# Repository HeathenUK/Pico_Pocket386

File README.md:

All credit to Ian Scott (https://github.com/polpo/picogus) and in turn to those he credits.

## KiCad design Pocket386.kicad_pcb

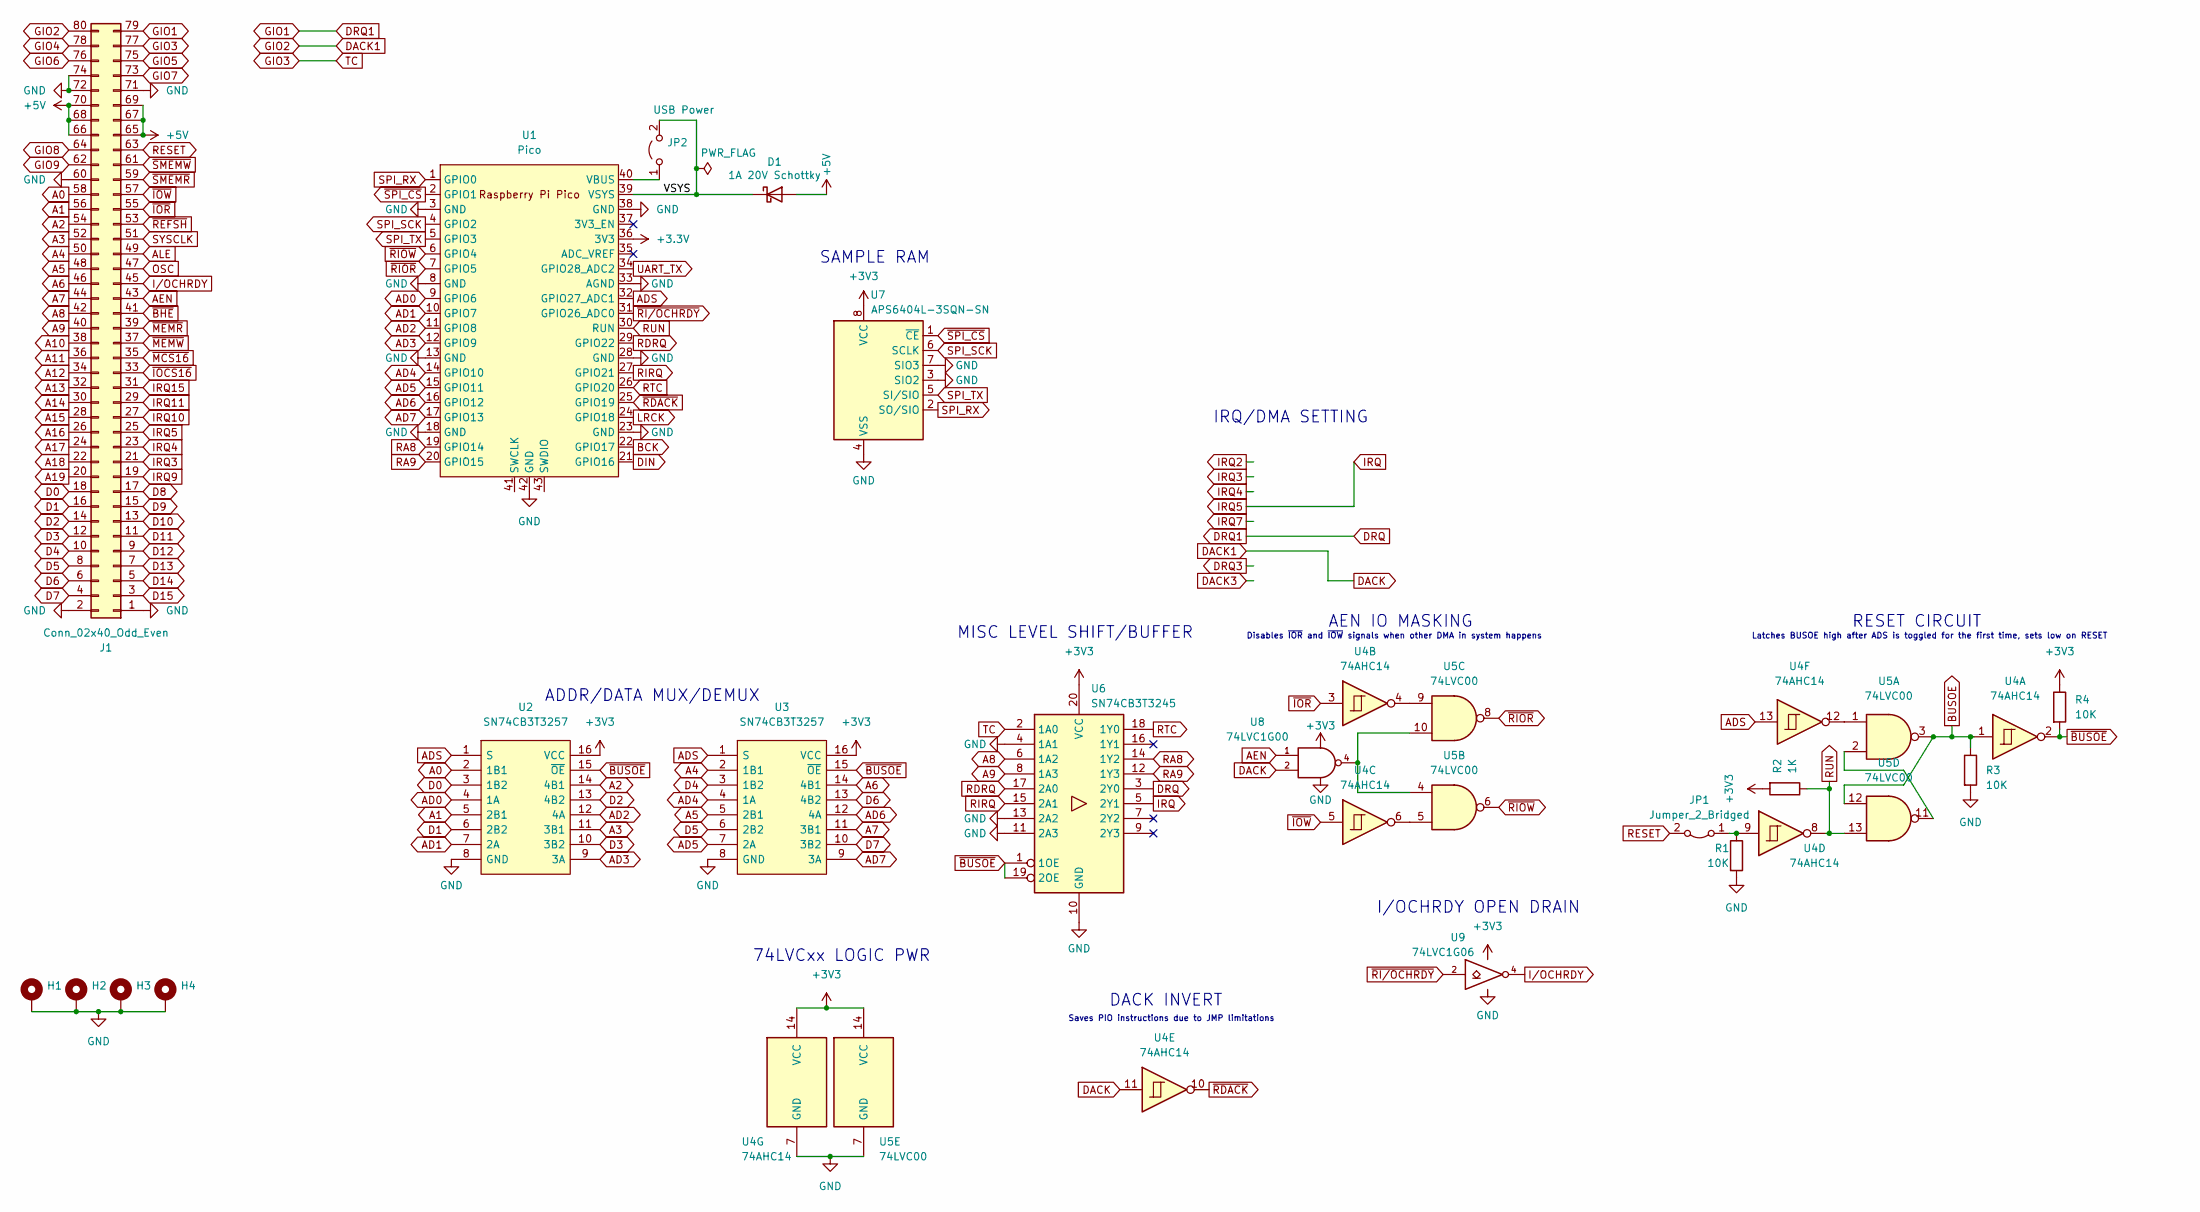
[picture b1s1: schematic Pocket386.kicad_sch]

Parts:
D1: 1A 20V Schottky; D_SOD-123
H1, H2, H3, H4: MountingHole_2.2mm_M2_Pad
J1: Conn_02x40_Odd_Even; XKB Male 80P 0.5P
JP1: Jumper_2_Bridged; PinHeader_1x02_P2.54mm_Vertical
JP2: USB Power; PinHeader_1x02_P2.54mm_Vertical
R1, R3, R4: 10K; R_0402_1005Metric
R2: 1K; R_0402_1005Metric
U1: Pico; RPi_Pico_SMD_TH
U2, U3: SN74CB3T3257; TSSOP-16_4.4x5mm_P0.65mm; Manufacturer_Part_Number 74FST3257DR2G; Mouser Part Number 863-74FST3257DR2G
U4: 74AHC14; TSSOP-14_4.4x5mm_P0.65mm
U5: 74LVC00; TSSOP-14_4.4x5mm_P0.65mm
U6: SN74CB3T3245; TSSOP-20_4.4x6.5mm_P0.65mm
U7: APS6404L-3SQN-SN; SOIC-8_3.9x4.9mm_P1.27mm
U8: 74LVC1G00; SOT-23-5
U9: 74LVC1G06; SOT-23-5

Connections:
+3.3V: U1.36 (3V3)
+3V3: R2.2, R4.1, U2.16 (VCC), U3.16 (VCC), U4.14 (VCC), U5.14 (VCC), U6.20 (VCC), U7.8 (VCC), U8.5 (VCC), U9.5 (VCC)
+5V: D1.2 (A), J1.65, J1.66, J1.67, J1.68, J1.69, J1.70
/VSYS: D1.1 (K), JP2.2 (B), U1.39 (VSYS)
A0: J1.58, U2.2 (1B1)
A1: J1.56, U2.5 (2B1)
A2: J1.54, U2.14 (4B1)
A3: J1.52, U2.11 (3B1)
A4: J1.50, U3.2 (1B1)
A5: J1.48, U3.5 (2B1)
A6: J1.46, U3.14 (4B1)
A7: J1.44, U3.11 (3B1)
A8: J1.42, U6.6 (1A2)
A9: J1.40, U6.8 (1A3)
A10: J1.38
A11: J1.36
A12: J1.34
A13: J1.32
A14: J1.30
A15: J1.28
A16: J1.26
A17: J1.24
A18: J1.22
A19: J1.20
AD0: U1.9 (GPIO6), U2.4 (1A)
AD1: U1.10 (GPIO7), U2.7 (2A)
AD2: U1.11 (GPIO8), U2.12 (4A)
AD3: U1.12 (GPIO9), U2.9 (3A)
AD4: U1.14 (GPIO10), U3.4 (1A)
AD5: U1.15 (GPIO11), U3.7 (2A)
AD6: U1.16 (GPIO12), U3.12 (4A)
AD7: U1.17 (GPIO13), U3.9 (3A)
ADS: U1.32 (GPIO27_ADC1), U2.1 (S), U3.1 (S), U4.13
AEN: J1.43, U8.1
ALE: J1.49
BCK: U1.22 (GPIO17)
BUSOE: R3.1, U4.1, U5.3, U5.12
D0: J1.18, U2.3 (1B2)
D1: J1.16, U2.6 (2B2)
D2: J1.14, U2.13 (4B2)
D3: J1.12, U2.10 (3B2)
D4: J1.10, U3.3 (1B2)
D5: J1.8, U3.6 (2B2)
D6: J1.6, U3.13 (4B2)
D7: J1.4, U3.10 (3B2)
D8: J1.17
D9: J1.15
D10: J1.13
D11: J1.11
D12: J1.9
D13: J1.7
D14: J1.5
D15: J1.3
DACK: J1.80, U4.11, U8.2
DIN: U1.21 (GPIO16)
DRQ: J1.79, U6.3 (2Y0)
GIO3: J1.77, U6.2 (1A0)
GIO4: J1.78
GIO5: J1.75
GIO6: J1.76
GIO7: J1.73
GIO8: J1.64
GIO9: J1.62
GND: H1.1, H2.1, H3.1, H4.1, J1.1, J1.2, J1.60, J1.71, J1.72, J1.74, R1.2, R3.2, U1.3 (GND), U1.8 (GND), U1.13 (GND), U1.18 (GND), U1.23 (GND), U1.28 (GND), U1.33 (AGND), U1.38 (GND), U1.42 (GND), U2.8 (GND), U3.8 (GND), U4.7 (GND), U5.7 (GND), U6.4 (1A1), U6.10 (GND), U6.11 (2A3), U6.13 (2A2), U7.3 (SIO2), U7.4 (VSS), U7.7 (SIO3), U8.3 (GND), U9.3 (GND)
IRQ: J1.25, U6.5 (2Y1)
IRQ3: J1.21
IRQ4: J1.23
IRQ9: J1.19
IRQ10: J1.27
IRQ11: J1.29
IRQ15: J1.31
I/OCHRDY: J1.45, U9.4
LRCK: U1.24 (GPIO18)
unnamed: JP1.1 (A), R1.1, U4.9
unnamed: JP2.1 (A), U1.40 (VBUS)
unnamed: U4.4, U5.9
unnamed: U4.6, U5.5
unnamed: U4.12, U5.1
unnamed: U5.4, U5.10, U8.4
unnamed: U5.2, U5.11
OSC: J1.47
RA8: U1.19 (GPIO14), U6.14 (1Y2)
RA9: U1.20 (GPIO15), U6.12 (1Y3)
RDRQ: U1.29 (GPIO22), U6.17 (2A0)
RESET: J1.63, JP1.2 (B)
RIRQ: U1.27 (GPIO21), U6.15 (2A1)
RTC: U1.26 (GPIO20), U6.18 (1Y0)
RUN: R2.1, U1.30 (RUN), U4.8, U5.13
SPI_RX: U1.1 (GPIO0), U7.2 (SO/SIO)
SPI_SCK: U1.4 (GPIO2), U7.6 (SCLK)
SPI_TX: U1.5 (GPIO3), U7.5 (SI/SIO)
SYSCLK: J1.51
UART_TX: U1.34 (GPIO28_ADC2)
~BHE: J1.41
~BUSOE: R4.2, U2.15 (~OE), U3.15 (~OE), U4.2, U6.1 (1OE), U6.19 (2OE)
~IOCS16: J1.33
~IOR: J1.55, U4.3
~IOW: J1.57, U4.5
~MCS16: J1.35
~MEMR: J1.39
~MEMW: J1.37
~RDACK: U1.25 (GPIO19), U4.10
~REFSH: J1.53
~RIOR: U1.7 (GPIO5), U5.8
~RIOW: U1.6 (GPIO4), U5.6
~RI/OCHRDY: U1.31 (GPIO26_ADC0), U9.2
~SMEMR: J1.59
~SMEMW: J1.61
~SPI_CS: U1.2 (GPIO1), U7.1 (~CE)

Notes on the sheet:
I/OCHRDY OPEN DRAIN
Saves PIO instructions due to JMP limitations
SAMPLE RAM
ADDR/DATA MUX/DEMUX
74LVCxx LOGIC PWR
RESET CIRCUIT
AEN IO MASKING
IRQ/DMA SETTING
Disables ~{IOR} and ~{IOW} signals when other DMA in system happens
DACK INVERT
Latches BUSOE high after ADS is toggled for the first time, sets low on RESET
MISC LEVEL SHIFT/BUFFER

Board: 2 copper layers, 21 parts (14 on the bottom side), 63 nets, no tracks yet.

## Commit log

2024-03-31 Update README.md
    Woops
2024-03-31 Add back [final?] signals?
